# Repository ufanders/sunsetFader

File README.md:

sunsetFader
===========

An artsy night-light that glows with the phases of a Puerto Rican sunset.

Read more about this projecgt on my blog here!: https://www.andersknelson.com/blog/?p=92

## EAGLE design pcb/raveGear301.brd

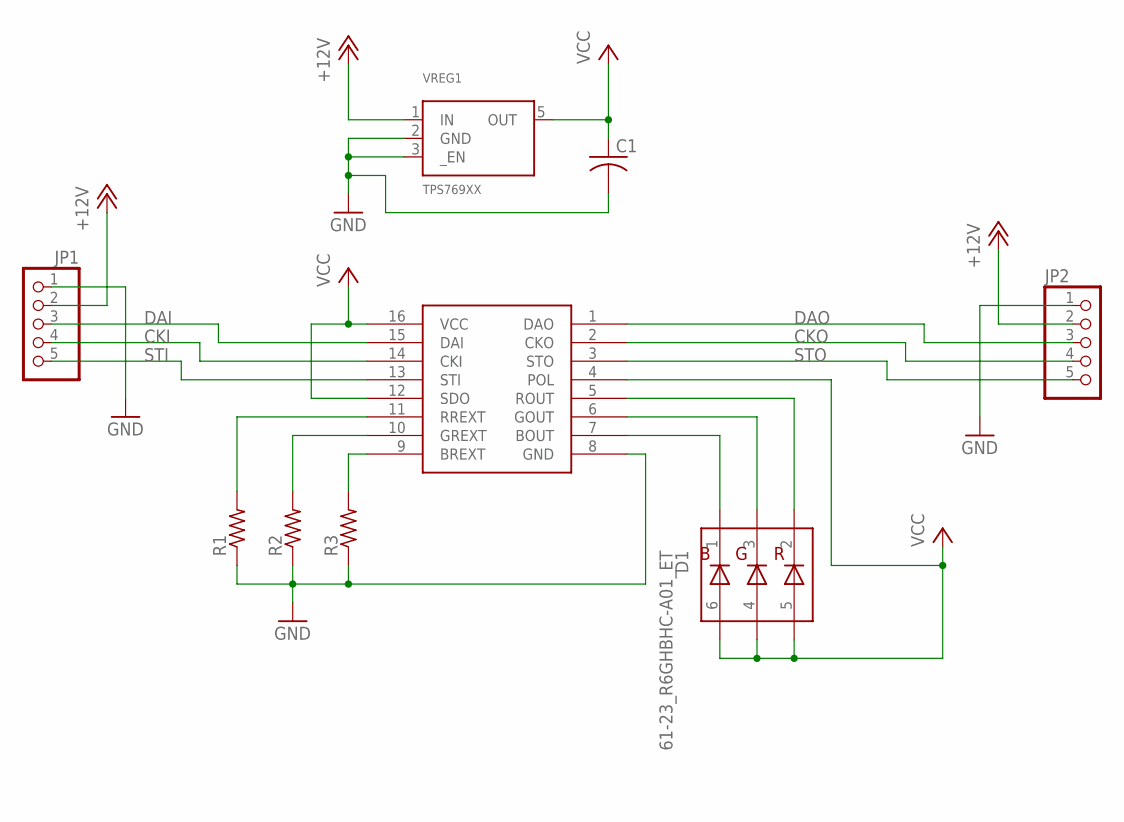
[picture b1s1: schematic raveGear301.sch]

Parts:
C1: C-USC0603; C0603
D1: 61-23_R6GHBHC-A01_ET; LF-6
JP1, JP2: PINHD-1X5; 1X05
R1, R2, R3: R-US_R0402; R0402
U1: DM412BEST; SSOP16
VREG1: TPS769XX; SOT23-5L

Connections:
+12V: JP1.2, JP2.2, VREG1.1 (IN)
BOUT: D1.1 (CB), U1.7 (BOUT)
BREXT: R3.2, U1.9 (BREXT)
CKI: JP1.4, U1.14 (CKI)
CKO: JP2.4, U1.2 (CKO)
DAI: JP1.3, U1.15 (DAI)
DAO: JP2.3, U1.1 (DAO)
GND: C1.2, JP1.1, JP2.1, R1.1, R2.1, R3.1, U1.8 (GND), VREG1.2 (GND), VREG1.3 (_EN)
GOUT: D1.3 (CG), U1.6 (GOUT)
GREXT: R2.2, U1.10 (GREXT)
ROUT: D1.2 (CR), U1.5 (ROUT)
RREXT: R1.2, U1.11 (RREXT)
STI: JP1.5, U1.13 (STI)
STO: JP2.5, U1.3 (STO)
VCC: C1.1, D1.4 (AG), D1.5 (AR), D1.6 (AB), U1.4 (POL), U1.12 (SDO), U1.16 (VCC), VREG1.5 (OUT)

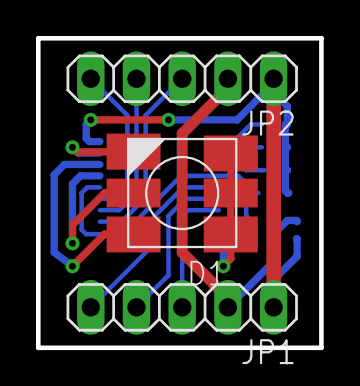
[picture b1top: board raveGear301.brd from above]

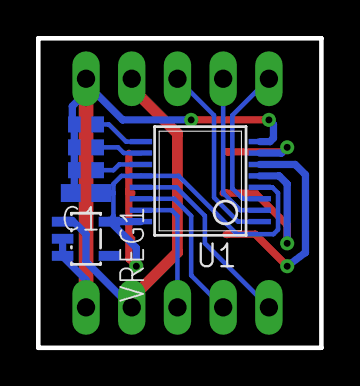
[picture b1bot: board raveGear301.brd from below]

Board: 2 copper layers, 15.7 x 17.2 mm, 9 parts (6 on the bottom side), 15 nets.

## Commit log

2014-07-31 -Updated gitignore
2014-07-31 -Builds and runs well. -No previous revisions seen in original SVN repo. -Fixed bad gitignore syntax.
2014-07-31 -Removed unnecessary source files.
2014-07-31 -Added PCB files.
2014-08-01 Syncing irritating file changes.
